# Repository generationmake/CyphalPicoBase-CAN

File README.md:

CyphalPicoBase/CAN
==================
Board for the Raspberry Pi Pico to connect via CAN using OpenCyphal and UCANPHY Micro.

You can buy one [here](https://cyphal.store/products/lxrobotics-cyphalpicobase-can) 💸.

## Description

The CyphalPicoBase/CAN provides the following functions:
* CAN connectivity to a OpenCyphal CAN bus using a Microchip MCP2515 CAN controller ([datasheet](https://ww1.microchip.com/downloads/en/DeviceDoc/MCP2515-Stand-Alone-CAN-Controller-with-SPI-20001801J.pdf))
* Onboard I2C EEPROM to store settings
* measurement of CAN bus voltage using GP26
* onboard temperature measurement using the internal temperature sensor of the Raspberry Pi Pico
* two status LEDs (D4 and D5)
* Raspberry Pi Pico directly mounted on bottom layer
* connectors to several external functions (see list below)

## Firmware
* [CyphalPicoBase-CAN-firmware](https://github.com/107-systems/CyphalPicoBase-CAN-firmware): This is the default firmware for this board. It enables all basic functions

## Pin Usage and connectors

### Raspberry Pi Pico (CN1)

| **Pin** | **Pin Name** | **Signal**    | **Description**                  |
|:-------:|:------------:|:-------------:|:--------------------------------:|
| 1       | GP0          | UART0_TX      | reserved for future use (GNSS)   |
| 2       | GP1          | UART0_RX      | reserved for future use (GNSS)   |
| 3       | GND          | GND           |                                  |
| 4       | GP2          |               |                                  |
| 5       | GP3          |               |                                  |
| 6       | GP4          | I2C0_SDA      | for eeprom and qwiic connector   |
| 7       | GP5          | I2C0_SCL      | for eeprom and qwiic connector   |
| 8       | GND          | GND           |                                  |
| 9       | GP6          | GPI0          | input 0                          |
| 10      | GP7          | GPI1          | input 1                          |
| 11      | GP8          | GPI2          | input 2                          |
| 12      | GP9          | GPI3          | input 3                          |
| 13      | GND          | GND           |                                  |
| 14      | GP10         | GPO0          | output 0                         |
| 15      | GP11         | GPO1          | output 1                         |
| 16      | GP12         | reserved      | Neopixel                         |
| 17      | GP13         | reserved      | radiation detector               |
| 18      | GND          | GND           |                                  |
| 19      | GP14         | SERVO0        | servo 0                          |
| 20      | GP15         | SERVO1        | servo 1                          |
| 21      | GP16         | SPI_MISO      | SPI for MCP2515                  |
| 22      | GP17         | MCP2515_CS    | SPI for MCP2515                  |
| 23      | GND          | GND           |                                  |
| 24      | GP18         | SPI_CLK       | SPI for MCP2515                  |
| 25      | GP19         | SPI_MOSI      | SPI for MCP2515                  |
| 26      | GP20         | MCP2515_INT   | interrupt for MCP2515            |
| 27      | GP21         | STATUS_LED2   | internal status LED 2            |
| 28      | GND          | GND           |                                  |
| 29      | GP22         | STATUS_LED3   | internal status LED 3            |
| 30      | RUN          | RESET         | Reset for Board                  |
| 31      | GP26         | INPUT_VOLTAGE | measure input voltage            |
| 32      | GP27         | ANALOG_INPUT0 | analog input                     |
| 33      | GND          | GND           |                                  |
| 34      | GP28         | ANALOG_INPUT1 | analog input                     |
| 35      | ADC_VREF     |               |                                  |
| 36      | 3V3 (OUT)    | 3V3-rail      | supply voltage for board         |
| 37      | 3V3_EN       |               |                                  |
| 38      | GND          | GND           |                                  |
| 39      | VSYS         |               |                                  |
| 40      | VBUS         | 5V-rail       | supply voltage for board         |

## Pinout

### I2C (CN2)

compatible to the Sparkfun qwiic standard (https://www.sparkfun.com/qwiic). JST SH 1mm 4-pin.

| pin number | signal        |
|:----------:|:-------------:|
| 1          | GND           |
| 2          | +3V3          |
| 3          | I2C_SDA       |
| 4          | I2C_SCL       |

### serial (CN3)

JST SH 1mm 4-pin.

| pin number | signal        |
|:----------:|:-------------:|
| 1          | GND           |
| 2          | +3V3          |
| 3          | SER_TX        |
| 4          | SER_RX        |

### CAN (CN4 and CN5)

UCANPHY Micro connector, according to the UCANPHY_Specification (https://forum.opencyphal.org/t/cyphal-can-physical-layer-specification-v1-0/1471). JST GH 1.25mm 4-pin.

| pin number | signal        |
|:----------:|:-------------:|
| 1          | +5V           |
| 2          | CANH          |
| 3          | CANL          |
| 4          | GND           |

### servo connector (CN7)

This is a regular 0.1-inch pin header.

Standard RC servos can be directly plugged into this connector

| pin number | signal        |
|:----------:|:-------------:|
| 1          | servo0        |
| 2          | servo1        |
| 3          | +5V           |
| 4          | +5V           |
| 5          | GND           |
| 6          | GND           |

### input/output connector (CN8)

This is a regular 0.1-inch pin header.

| pin number | signal        |
|:----------:|:-------------:|
| 1          | +5V           |
| 2          | GND           |
| 3          | ANALOG_INPUT1 |
| 4          | GND           |
| 5          | ANALOG_INPUT0 |
| 6          | GND           |
| 7          | INPUT0        |
| 8          | GND           |
| 9          | INPUT1        |
| 10         | GND           |
| 11         | INPUT2        |
| 12         | GND           |
| 13         | INPUT3        |
| 14         | GND           |
| 15         | OUTPUT0       |
| 16         | GND           |
| 17         | OUTPUT1       |
| 18         | GND           |
| 19         | +5V           |
| 20         | GND           |
| 21         | +3.3V         |
| 22         | GND           |
| 23         | RESERVED0     |
| 24         | GND           |
| 25         | NEOPIXEL      |
| 26         | GND           |

+5V can be fed over this connector to the servo connector (CN7) and the neopixel connector (CN12) if power supply over the CAN connector is not sufficicant.

### neopixel connector (CN12)

connector for Adafruit Neopixel RGB leds (https://learn.adafruit.com/adafruit-neopixel-uberguide/the-magic-of-neopixels). JST PH 2mm 3-pin.

| pin number | signal        |
|:----------:|:-------------:|
| 1          | neopixel      |
| 2          | +5V           |
| 3          | GND           |

## enclosure

There exists a 3D printable enclosure to encapsulate the PCB.

## PCB
### Top

### Bottom

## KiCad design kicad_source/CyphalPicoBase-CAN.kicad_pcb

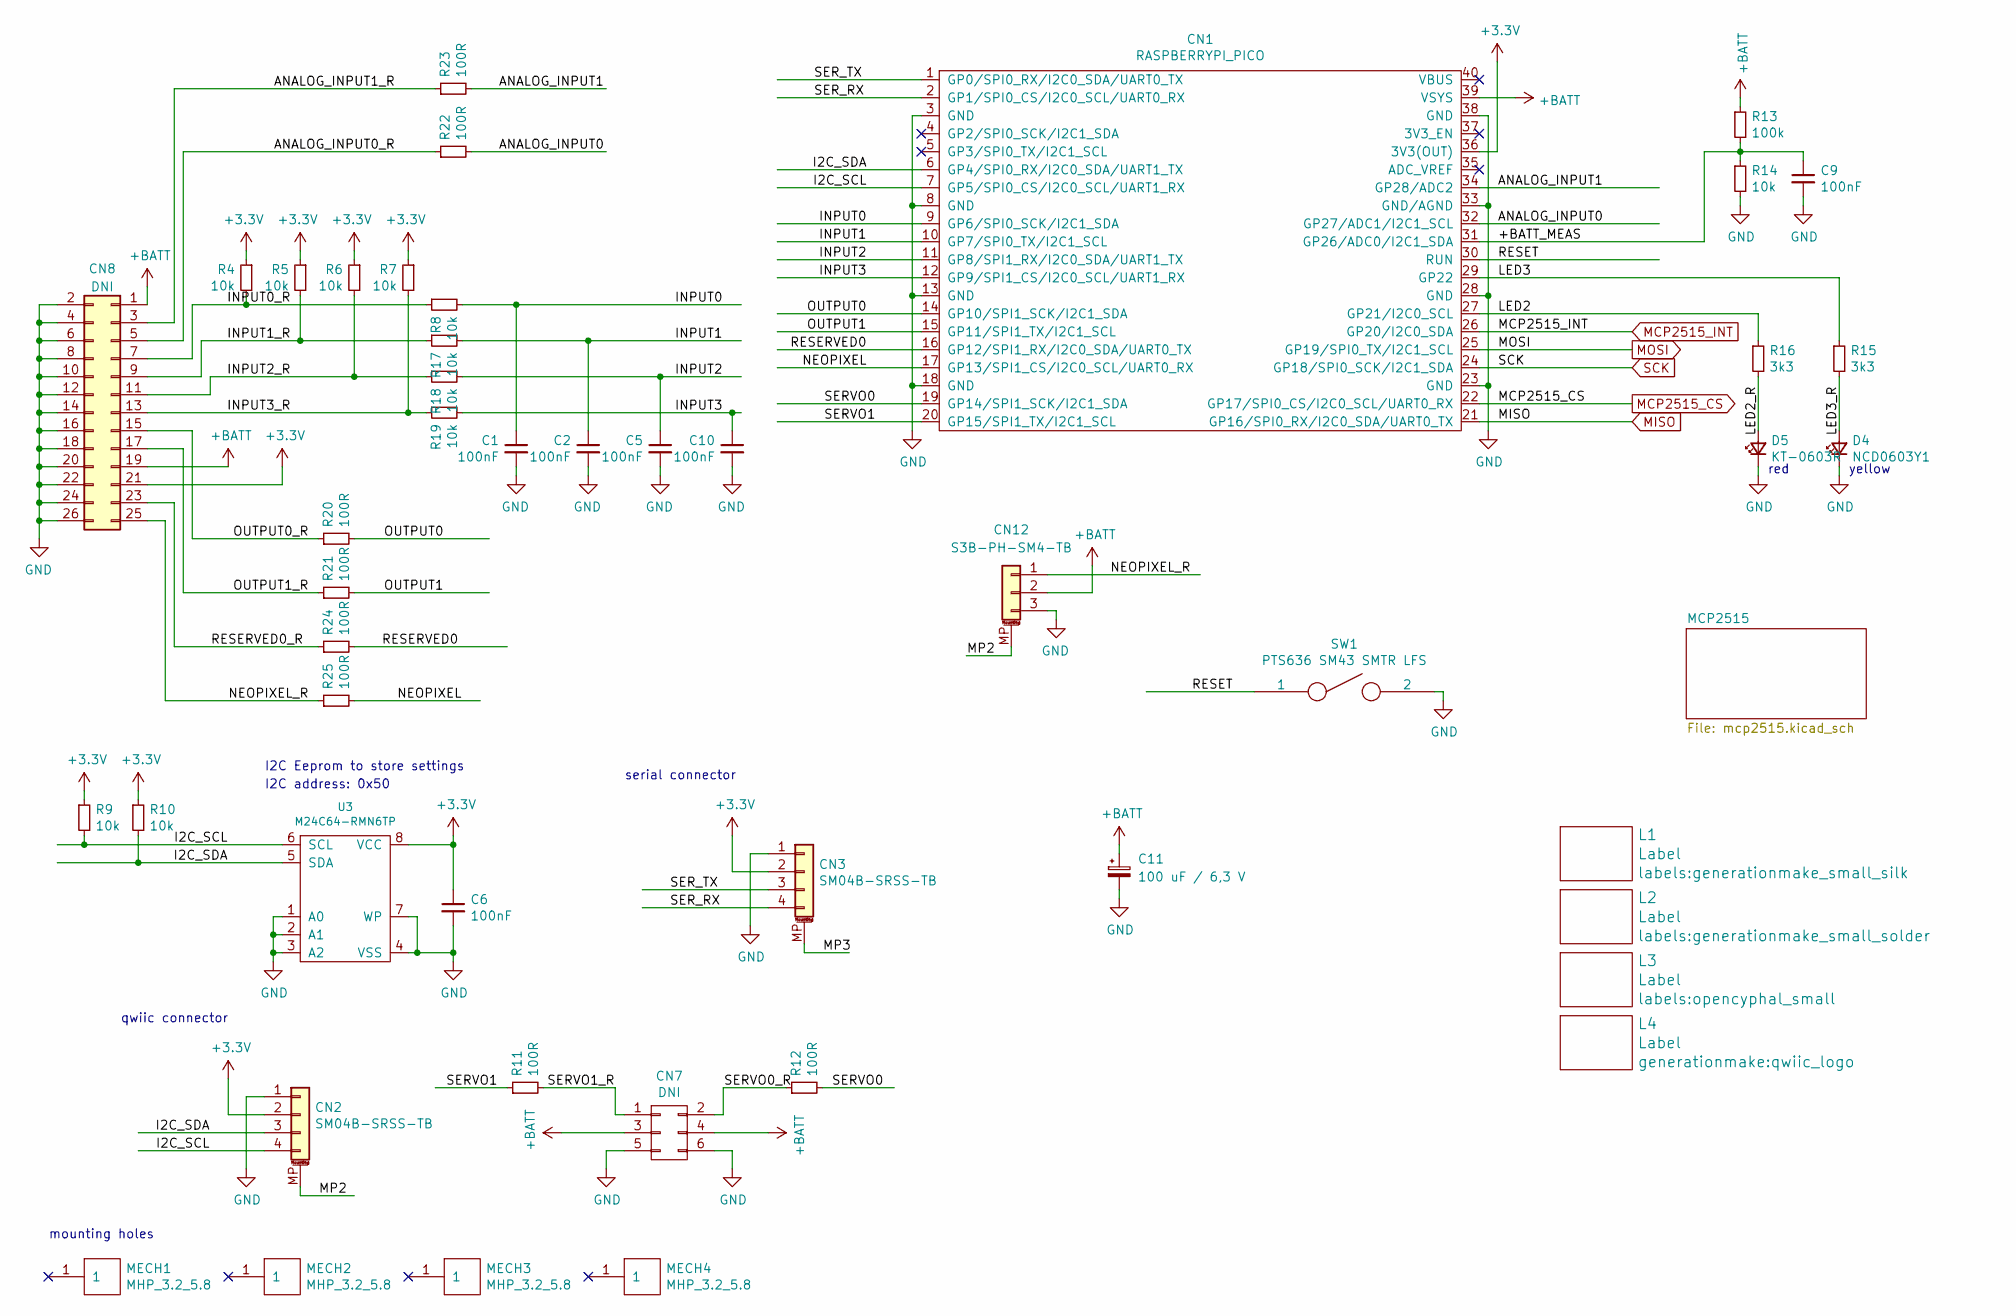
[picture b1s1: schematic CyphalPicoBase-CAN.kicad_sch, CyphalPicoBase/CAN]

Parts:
C1, C2, C5, C6, C9, C10: 100nF; C_0603_1608Metric; LCSC C14663
C11: 100 uF / 6,3 V; CP_Elec_5x5.3; LCSC C3001204
CN1: RASPBERRYPI_PICO; RASPI_PICO_SOLDER_Kopie
CN2, CN3: SM04B-SRSS-TB; JST_SH_SM04B-SRSS-TB_1x04-1MP_P1.00mm_Horizontal; LCSC C160404
CN7: DNI; PinHeader_2x03_P2.54mm_Horizontal
CN8: DNI; PinHeader_2x13_P2.54mm_Vertical
CN12: S3B-PH-SM4-TB; JST_PH_S3B-PH-SM4-TB_1x03-1MP_P2.00mm_Horizontal; LCSC C265101
D4: NCD0603Y1; LED_0603_1608Metric; LCSC C84268
D5: KT-0603R; LED_0603_1608Metric; LCSC C2286
L1: Label; generationmake_small_silk
L2: Label; generationmake_small_solder
L3: Label; opencyphal_small
L4: Label; qwiic_logo
MECH1, MECH2, MECH3, MECH4: MHP_3.2_5.8
R4, R5, R6, R7, R8, R9, R10, R14, R17, R18, R19: 10k; R_0603_1608Metric; LCSC C25804
R11, R12, R20, R21, R22, R23, R24, R25: 100R; R_0603_1608Metric; LCSC C22775
R13: 100k; R_0603_1608Metric; LCSC C25803
R15, R16: 3k3; R_0603_1608Metric; LCSC C22978
SW1: PTS636 SM43 SMTR LFS; SW_SPST_CK_RS282G05A3; LCSC C2800965
U3: M24C64-RMN6TP; SOIC-8_3.9x4.9mm_P1.27mm; LCSC C79988

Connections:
+3V3: C6.1, CN1.36 (3V3(OUT)), CN2.2, CN3.2, CN8.21, R4.1, R5.1, R6.1, R7.1, R9.1, R10.1, U3.8 (VCC); also elsewhere on the board
+BATT: C11.1, CN1.39 (VSYS), CN7.3, CN7.4, CN8.1, CN8.19, CN12.2, R13.1; also elsewhere on the board
/+BATT_MEAS: C9.1, CN1.31 (GP26/ADC0/I2C1_SDA), R13.2, R14.1
/ANALOG_INPUT0: CN1.32 (GP27/ADC1/I2C1_SCL), R22.2
/ANALOG_INPUT0_R: CN8.5, R22.1
/ANALOG_INPUT1: CN1.34 (GP28/ADC2), R23.2
/ANALOG_INPUT1_R: CN8.3, R23.1
/I2C_SCL: CN1.7 (GP5/SPI0_CS/I2C0_SCL/UART1_RX), CN2.4, R9.2, U3.6 (SCL)
/I2C_SDA: CN1.6 (GP4/SPI0_RX/I2C0_SDA/UART1_TX), CN2.3, R10.2, U3.5 (SDA)
/INPUT0: C1.1, CN1.9 (GP6/SPI0_SCK/I2C1_SDA), R8.2
/INPUT0_R: CN8.7, R4.2, R8.1
/INPUT1: C2.1, CN1.10 (GP7/SPI0_TX/I2C1_SCL), R17.2
/INPUT1_R: CN8.9, R5.2, R17.1
/INPUT2: C5.1, CN1.11 (GP8/SPI1_RX/I2C0_SDA/UART1_TX), R18.2
/INPUT2_R: CN8.11, R6.2, R18.1
/INPUT3: C10.1, CN1.12 (GP9/SPI1_CS/I2C0_SCL/UART1_RX), R19.2
/INPUT3_R: CN8.13, R7.2, R19.1
/LED2: CN1.27 (GP21/I2C0_SCL), R16.1
/LED2_R: D5.2 (A), R16.2
/LED3: CN1.29 (GP22), R15.1
/LED3_R: D4.2 (A), R15.2
/MP2: CN2.MP (MountPin), CN12.MP (MountPin)
/MP3: CN3.MP (MountPin)
/NEOPIXEL: CN1.17 (GP13/SPI1_CS/I2C0_SCL/UART0_RX), R25.2
/NEOPIXEL_R: CN8.25, CN12.1, R25.1
/OUTPUT0: CN1.14 (GP10/SPI1_SCK/I2C1_SDA), R20.2
/OUTPUT0_R: CN8.15, R20.1
/OUTPUT1: CN1.15 (GP11/SPI1_TX/I2C1_SCL), R21.2
/OUTPUT1_R: CN8.17, R21.1
/RESERVED0: CN1.16 (GP12/SPI1_RX/I2C0_SDA/UART0_TX), R24.2
/RESERVED0_R: CN8.23, R24.1
/RESET: CN1.30 (RUN), SW1.1
/SERVO0: CN1.19 (GP14/SPI1_SCK/I2C1_SDA), R12.2
/SERVO0_R: CN7.2, R12.1
/SERVO1: CN1.20 (GP15/SPI1_TX/I2C1_SCL), R11.1
/SERVO1_R: CN7.1, R11.2
/SER_RX: CN1.2 (GP1/SPI0_CS/I2C0_SCL/UART0_RX), CN3.4
/SER_TX: CN1.1 (GP0/SPI0_RX/I2C0_SDA/UART0_TX), CN3.3
GND: C1.2, C2.2, C5.2, C6.2, C9.2, C10.2, C11.2, CN1.3 (GND), CN1.8 (GND), CN1.13 (GND), CN1.18 (GND), CN1.23 (GND), CN1.28 (GND), CN1.33 (GND/AGND), CN1.38 (GND), CN2.1, CN3.1, CN7.5, CN7.6, CN8.2, CN8.4, CN8.6, CN8.8, CN8.10, CN8.12, CN8.14, CN8.16, CN8.18, CN8.20, CN8.22, CN8.24, CN8.26, CN12.3, D4.1 (K), D5.1 (K), R14.2, SW1.2, U3.1 (A0), U3.2 (A1), U3.3 (A2), U3.4 (VSS), U3.7 (WP); also elsewhere on the board
MCP2515_CS: CN1.22 (GP17/SPI0_CS/I2C0_SCL/UART0_RX); also elsewhere on the board
MCP2515_INT: CN1.26 (GP20/I2C0_SDA); also elsewhere on the board
MISO: CN1.21 (GP16/SPI0_RX/I2C0_SDA/UART0_TX); also elsewhere on the board
MOSI: CN1.25 (GP19/SPI0_TX/I2C1_SCL); also elsewhere on the board
SCK: CN1.24 (GP18/SPI0_SCK/I2C1_SDA); also elsewhere on the board

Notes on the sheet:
yellow
serial connector
qwiic connector
mounting holes
red
I2C address: 0x50
I2C Eeprom to store settings

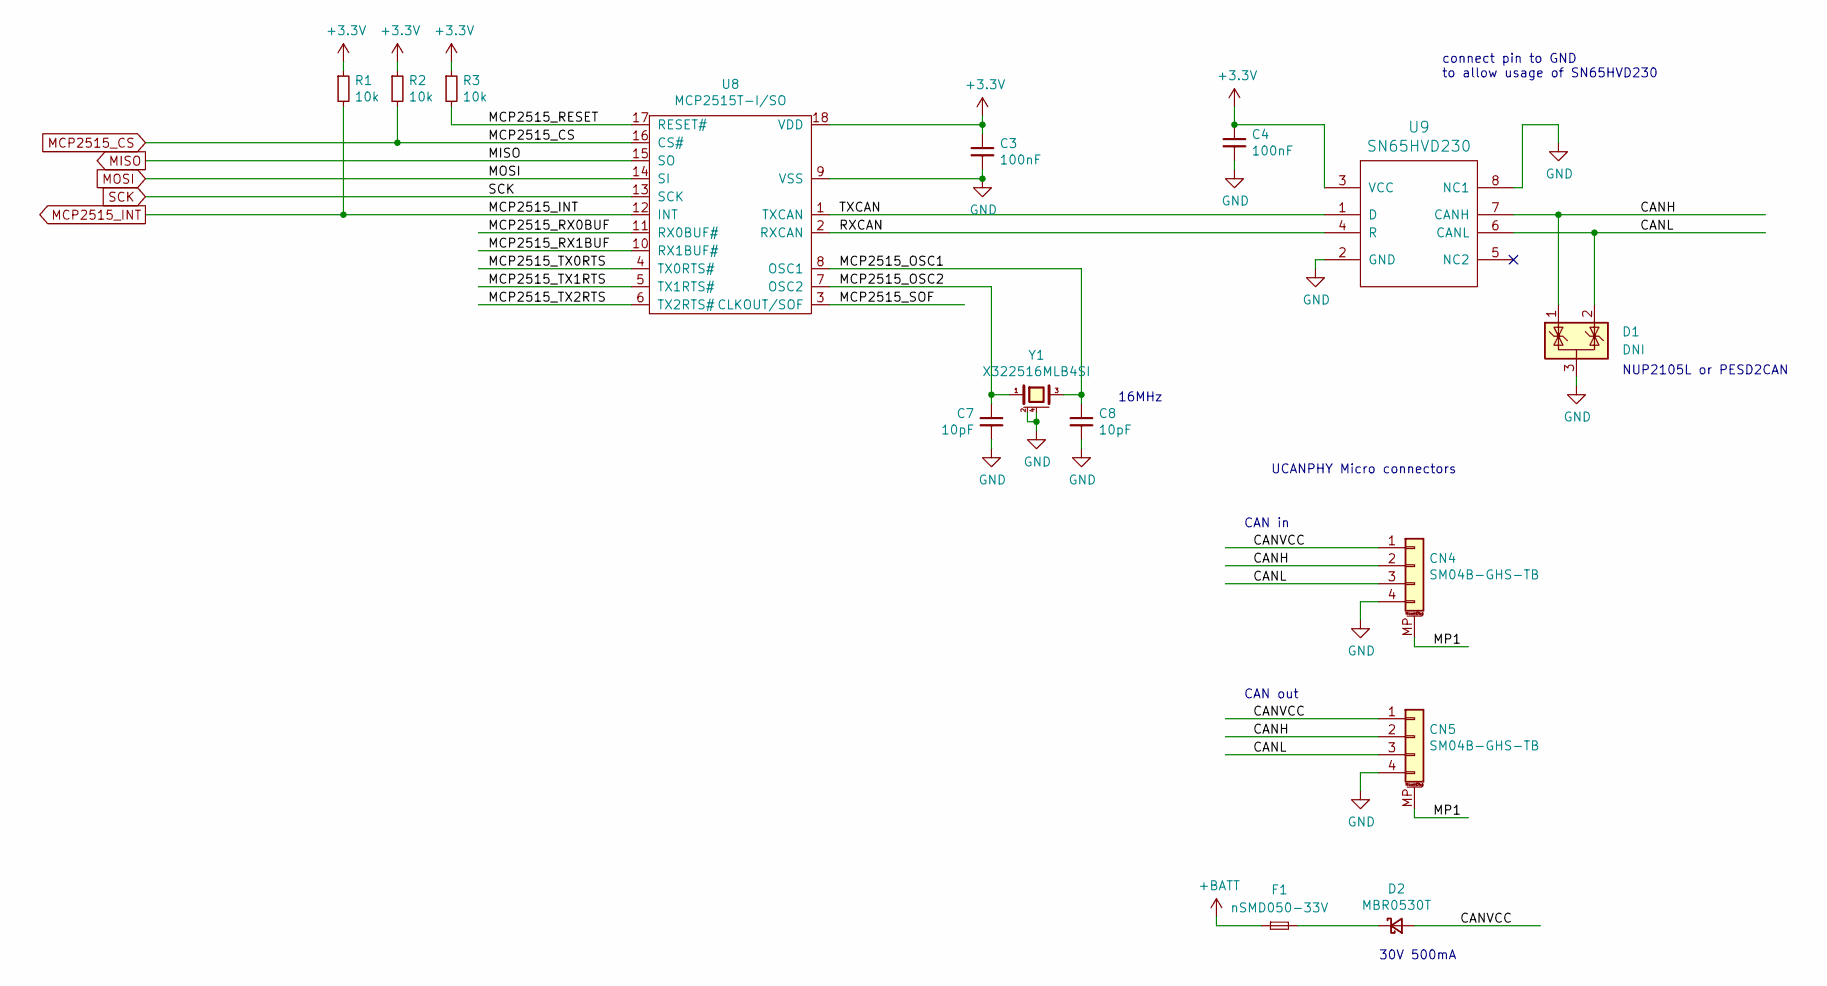
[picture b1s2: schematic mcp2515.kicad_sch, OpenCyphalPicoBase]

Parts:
C3, C4: 100nF; C_0603_1608Metric; LCSC C14663
C7, C8: 10pF; C_0603_1608Metric; LCSC C1634
CN4, CN5: SM04B-GHS-TB; JST_GH_SM04B-GHS-TB_1x04-1MP_P1.25mm_Horizontal; LCSC C189895
D1: DNI; SOT-23
D2: MBR0530T; D_SOD-123; LCSC C77336
F1: nSMD050-33V; Fuse_1206_3216Metric; LCSC C70077
R1, R2, R3: 10k; R_0603_1608Metric; LCSC C25804
U8: MCP2515T-I/SO; SOIC-18W_7.5x11.6mm_P1.27mm; LCSC C153782
U9: SN65HVD230; SOIC-8_3.9x4.9mm_P1.27mm; LCSC C12084
Y1: X322516MLB4SI; Crystal_SMD_3.2x2.5mm_4Pad; LCSC C13738

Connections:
+3V3: C3.1, C4.1, R1.1, R2.1, R3.1, U8.18 (VDD), U9.3 (VCC); also elsewhere on the board
+BATT: F1.1; also elsewhere on the board
/MCP2515/CANH: CN4.2, CN5.2, D1.1 (K), U9.7 (CANH)
/MCP2515/CANL: CN4.3, CN5.3, D1.2 (K), U9.6 (CANL)
/MCP2515/CANVCC: CN4.1, CN5.1, D2.2 (A)
/MCP2515/MCP2515_OSC1: C8.1, U8.8 (OSC1), Y1.3
/MCP2515/MCP2515_OSC2: C7.1, U8.7 (OSC2), Y1.1
/MCP2515/MCP2515_RESET: R3.2, U8.17 (RESET#)
/MCP2515/MCP2515_RX0BUF: U8.11 (RX0BUF#)
/MCP2515/MCP2515_RX1BUF: U8.10 (RX1BUF#)
/MCP2515/MCP2515_SOF: U8.3 (CLKOUT/SOF)
/MCP2515/MCP2515_TX0RTS: U8.4 (TX0RTS#)
/MCP2515/MCP2515_TX1RTS: U8.5 (TX1RTS#)
/MCP2515/MCP2515_TX2RTS: U8.6 (TX2RTS#)
/MCP2515/MP1: CN4.MP (MountPin), CN5.MP (MountPin)
/MCP2515/RXCAN: U8.2 (RXCAN), U9.4 (R)
/MCP2515/TXCAN: U8.1 (TXCAN), U9.1 (D)
GND: C3.2, C4.2, C7.2, C8.2, CN4.4, CN5.4, D1.3 (A), U8.9 (VSS), U9.2 (GND), U9.8 (NC1), Y1.2 (case), Y1.4 (case); also elsewhere on the board
MCP2515_CS: R2.2, U8.16 (CS#); also elsewhere on the board
MCP2515_INT: R1.2, U8.12 (INT); also elsewhere on the board
MISO: U8.15 (SO); also elsewhere on the board
MOSI: U8.14 (SI); also elsewhere on the board
unnamed: D2.1 (K), F1.2
SCK: U8.13 (SCK); also elsewhere on the board

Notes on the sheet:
16MHz
NUP2105L or PESD2CAN
connect pin to GND to allow usage of SN65HVD230
UCANPHY Micro connectors
30V 500mA
CAN in
CAN out

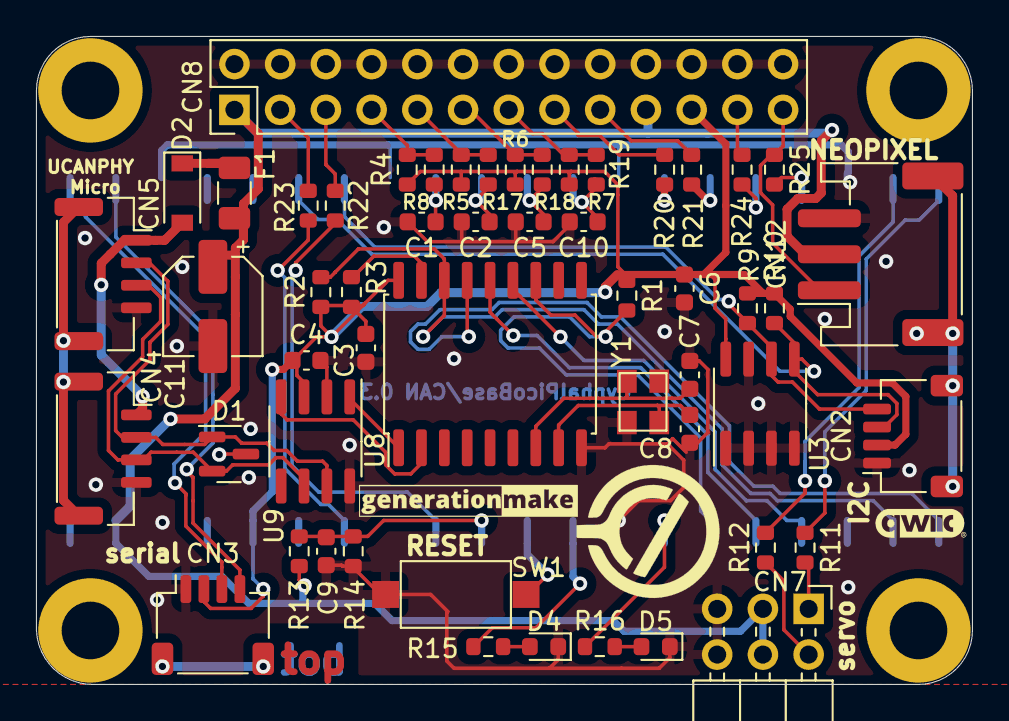
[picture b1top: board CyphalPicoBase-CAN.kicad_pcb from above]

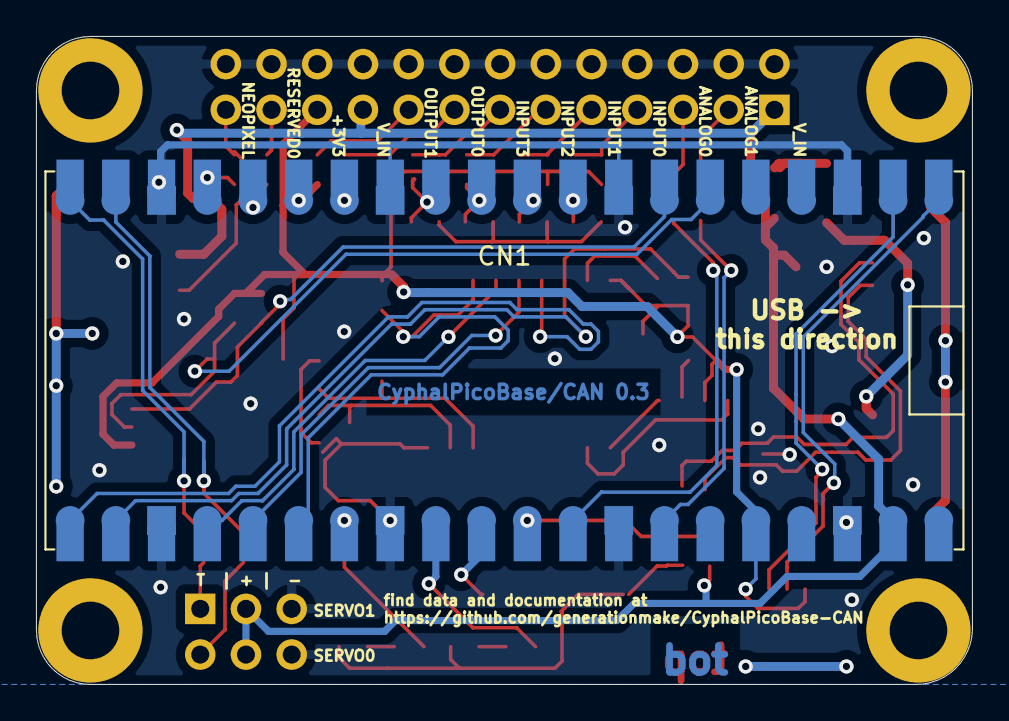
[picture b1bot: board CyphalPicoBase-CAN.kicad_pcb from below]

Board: 2 copper layers, 52.0 x 36.0 mm, 62 parts (2 on the bottom side), 53 nets.

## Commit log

2022-06-06 added first draft of schematic and layout
2022-06-06 added schematic pdf and images
2022-06-08 updated layout, added connectors for input and output
2022-06-09 added screw terminals for CAN
2022-06-09 added solder pads for raspberry pi pico
2022-06-09 updated schematic pdf and images, made DRC
2022-10-09 saved project with kicad 6
2022-10-09 removed some tht parts
2022-10-21 switched Raspberry Pi Pico to direct solder only
2022-10-21 reworked library references
2022-10-22 changed some connectors
2022-10-22 added NeoPixel connector, updated layout
2022-10-23 fixed some drc errors
2022-10-23 updated images
2022-10-23 switched servos to +BATT to power them from CAN bus
2022-10-23 updated schematic pdf
2022-10-25 added poly fuse
2022-10-26 added capacitor on +BATT
2022-10-26 added 3d model of raspberry pi pico
2022-10-26 updated DRC
2023-01-08 added step file and freecad project
2023-01-09 updated enclosure
2023-01-09 added 3d print production data
2023-01-20 Updating link to firmware.
2023-01-21 added screw holes
2023-01-21 updated production data
2023-01-24 Adding Prusa Slicer projects and GCode.
2023-01-25 increased the cut out for the USB connector
2023-04-16 added license
2023-04-16 clearified some part numbers
2023-06-03 added pinout information
2023-06-03 updated pinout information
2023-06-04 added description to Readme
2023-06-04 made more space for boot sel button
2023-06-04 added small standoffs to position PCB
2023-08-03 generated gerber files
2023-08-03 added gerber zip file
2023-08-03 added some JLCPCB part numbers and BOM
2023-08-03 added placement file
2023-08-06 removed unnecessary files
2023-08-06 added missing JLCPCB part numbers
2023-08-06 switched to JLCPCB basic parts where possible
2023-08-08 combined CN6, CN8 and CN11 into one connector
2023-08-08 removed C12, added CAN protection, updated schematic
2023-08-09 added qwiic logo, made DRC
2023-08-09 generated gerber and production data
2023-08-09 corrected BOM
2023-08-11 updated images and schematic pdf
2023-08-11 updated step file
2023-09-21 renamed files
2023-09-21 reworked readme
2023-09-21 updated labels in schematic, updated pdf and images
2023-09-21 updated gerber files
2023-09-21 added pdf with dimension
2023-09-21 updated pdf with dimension
2023-11-18 updated enclosure top, added cutout for neopixel connector, made cut into standoff near serial connector
2023-11-19 updated step file of PCB, added JST conectors
2023-11-19 reworked enclosure top
2023-11-20 added cut out for capacitor
2023-11-20 added image with connectors
2023-11-21 added connector housings to the 3d model, increased hole for serial connector
2023-12-06 Add link to Cyphal.Store.
2023-12-06 Add new line.
2023-12-06 Add link to Cyphal.Store. (#27)
